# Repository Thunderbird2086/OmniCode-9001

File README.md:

# OmniCode:9001
A modular keyboard made up of three detachable untis.

*POGO pins are rendered with 5 pins only*

## Overview
OmniCode:9001 is the modular keyboards born in Hong Kong, engineered for control beyond limits. This highly customizable, open-source keyboard is designed for ergonomic comfort, maximum flexibility, and creative power. With magnetic connectors, hot-swappable blocks like GlyphMatrix, PhaseShift, and DeltaForm, OmniCode:9001 adapts to every workflow.  It is built with the RP2040 microcontroller for next-generation performance.  Ideal for makers and keyboard enthusiasts who demand the best.

## Sub Modules
- **Alpha Block:** GlyphMatrix taps into the visual power of language—glyphs as symbols, matrix as command stream. It’s the scriptwriter for your digital world.

- **Nav Block:** PhaseShift suggests rapid movement, shifting through modes or layers like teleportation. It’s your tactical array for traversing digital dimensions.

- **Num Block:** DeltaForm Already perfect. This name suggests modular transformation. Zoom, macros, data entry and it's all reborn in a shapeshifting format.

## Builds
* [BOM](bom/)
* [Build guides](doc/build.md)
* [Cases](cases/)

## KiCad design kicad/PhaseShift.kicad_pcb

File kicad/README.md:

# OmniCode:9001 PCB Designs

This directory contains all KiCad PCB design files for the OmniCode:9001 keyboard modules.

## Modules

### GlyphMatrix (Alpha Block)
The main typing module with a full ANSI layout.

**Features:**
- RP2040 microcontroller
- USB Type-C connector
- Hot-swappable MX switch sockets
- RGB LED support
- POGO pin connections for modular attachment

### PhaseShift (Nav Block)
Navigation and macro control module.

**Features:**
- Hot-swappable MX switch sockets
- RGB LED support
- POGO pin connections for modular attachment

### DeltaForm (Num Block)
Numeric keypad and additional macro keys.

**Features:**
- Hot-swappable MX switch sockets
- RGB LED support
- POGO pin connections for modular attachment

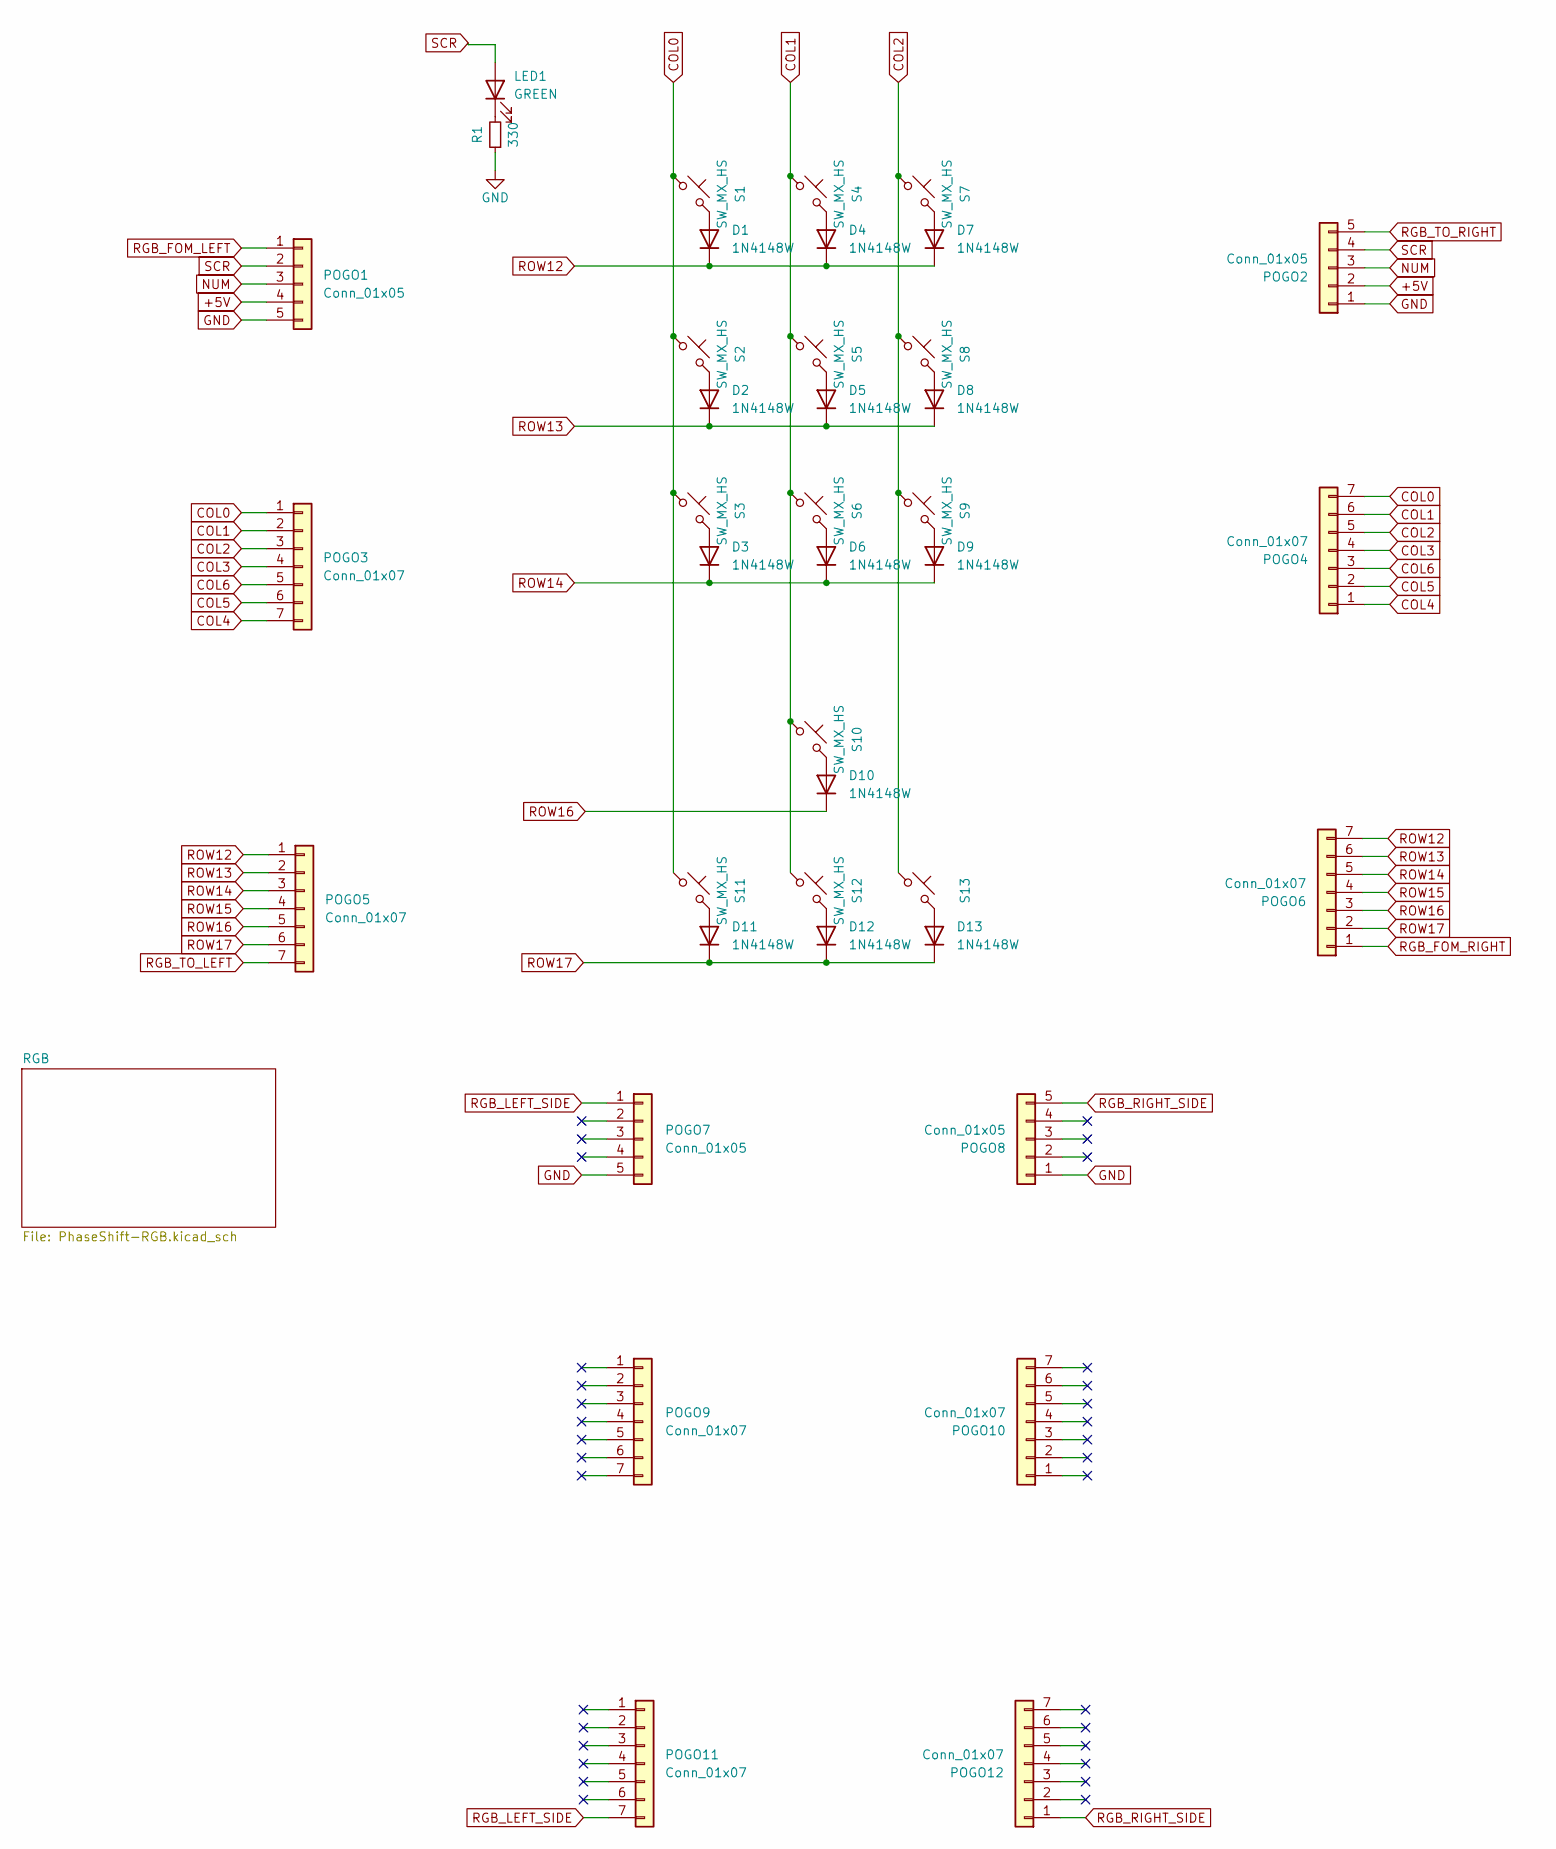
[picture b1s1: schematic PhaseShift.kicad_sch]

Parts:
D1, D2, D3, D4, D5, D6, D7, D8, D9, D10, D11, D12, D13: 1N4148W; D3_SMD; LCSC C7420318
LED1: GREEN; LED_0603_1608Metric_Pad1.05x0.95mm_HandSolder; LCSC C84264
POGO1, POGO2: Conn_01x05; Pogopin_1x05_P2.54mm_Curved
POGO3, POGO4, POGO5, POGO6: Conn_01x07; Pogopin_1x07_P2.54mm_Curved
POGO7, POGO8: Conn_01x05; Pogopin_1x05_P2.54mm
POGO9, POGO10, POGO11, POGO12: Conn_01x07; Pogopin_1x07_P2.54mm
R1: 330; R_0603_1608Metric; LCSC C23138
S1, S2, S3, S4, S5, S6, S7, S8, S9, S10, S11, S12: SW_MX_HS; SW_MX_HS_1u; LCSC C9900021274
S13: SW_MX_HS_1u; LCSC C9900021274

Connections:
+5V: POGO1.4, POGO2.2; also elsewhere on the board
COL0: POGO3.1, POGO4.7, S1.2, S2.2, S3.2, S11.2
COL1: POGO3.2, POGO4.6, S4.2, S5.2, S6.2, S10.2, S12.2
COL2: POGO3.3, POGO4.5, S7.2, S8.2, S9.2, S13.2
COL3: POGO3.4, POGO4.4
COL4: POGO3.7, POGO4.1
COL5: POGO3.6, POGO4.2
COL6: POGO3.5, POGO4.3
GND: POGO1.5, POGO2.1, POGO7.5, POGO8.1, R1.1; also elsewhere on the board
NUM: POGO1.3, POGO2.3
unnamed: D1.2 (A), S1.1
unnamed: D2.2 (A), S2.1
unnamed: D3.2 (A), S3.1
unnamed: D4.2 (A), S4.1
unnamed: D5.2 (A), S5.1
unnamed: D6.2 (A), S6.1
unnamed: D7.2 (A), S7.1
unnamed: D8.2 (A), S8.1
unnamed: D9.2 (A), S9.1
unnamed: D10.2 (A), S10.1
unnamed: D11.2 (A), S11.1
unnamed: D12.2 (A), S12.1
unnamed: D13.2 (A), S13.1
unnamed: LED1.1 (K), R1.2
RGB_FOM_LEFT: POGO1.1; also elsewhere on the board
RGB_FOM_RIGHT: POGO6.1; also elsewhere on the board
RGB_LEFT_SIDE: POGO7.1, POGO11.7
RGB_RIGHT_SIDE: POGO8.5, POGO12.1
RGB_TO_LEFT: POGO5.7; also elsewhere on the board
RGB_TO_RIGHT: POGO2.5; also elsewhere on the board
ROW12: D1.1 (K), D4.1 (K), D7.1 (K), POGO5.1, POGO6.7
ROW13: D2.1 (K), D5.1 (K), D8.1 (K), POGO5.2, POGO6.6
ROW14: D3.1 (K), D6.1 (K), D9.1 (K), POGO5.3, POGO6.5
ROW15: POGO5.4, POGO6.4
ROW16: D10.1 (K), POGO5.5, POGO6.3
ROW17: D11.1 (K), D12.1 (K), D13.1 (K), POGO5.6, POGO6.2
SCR: LED1.2 (A), POGO1.2, POGO2.4

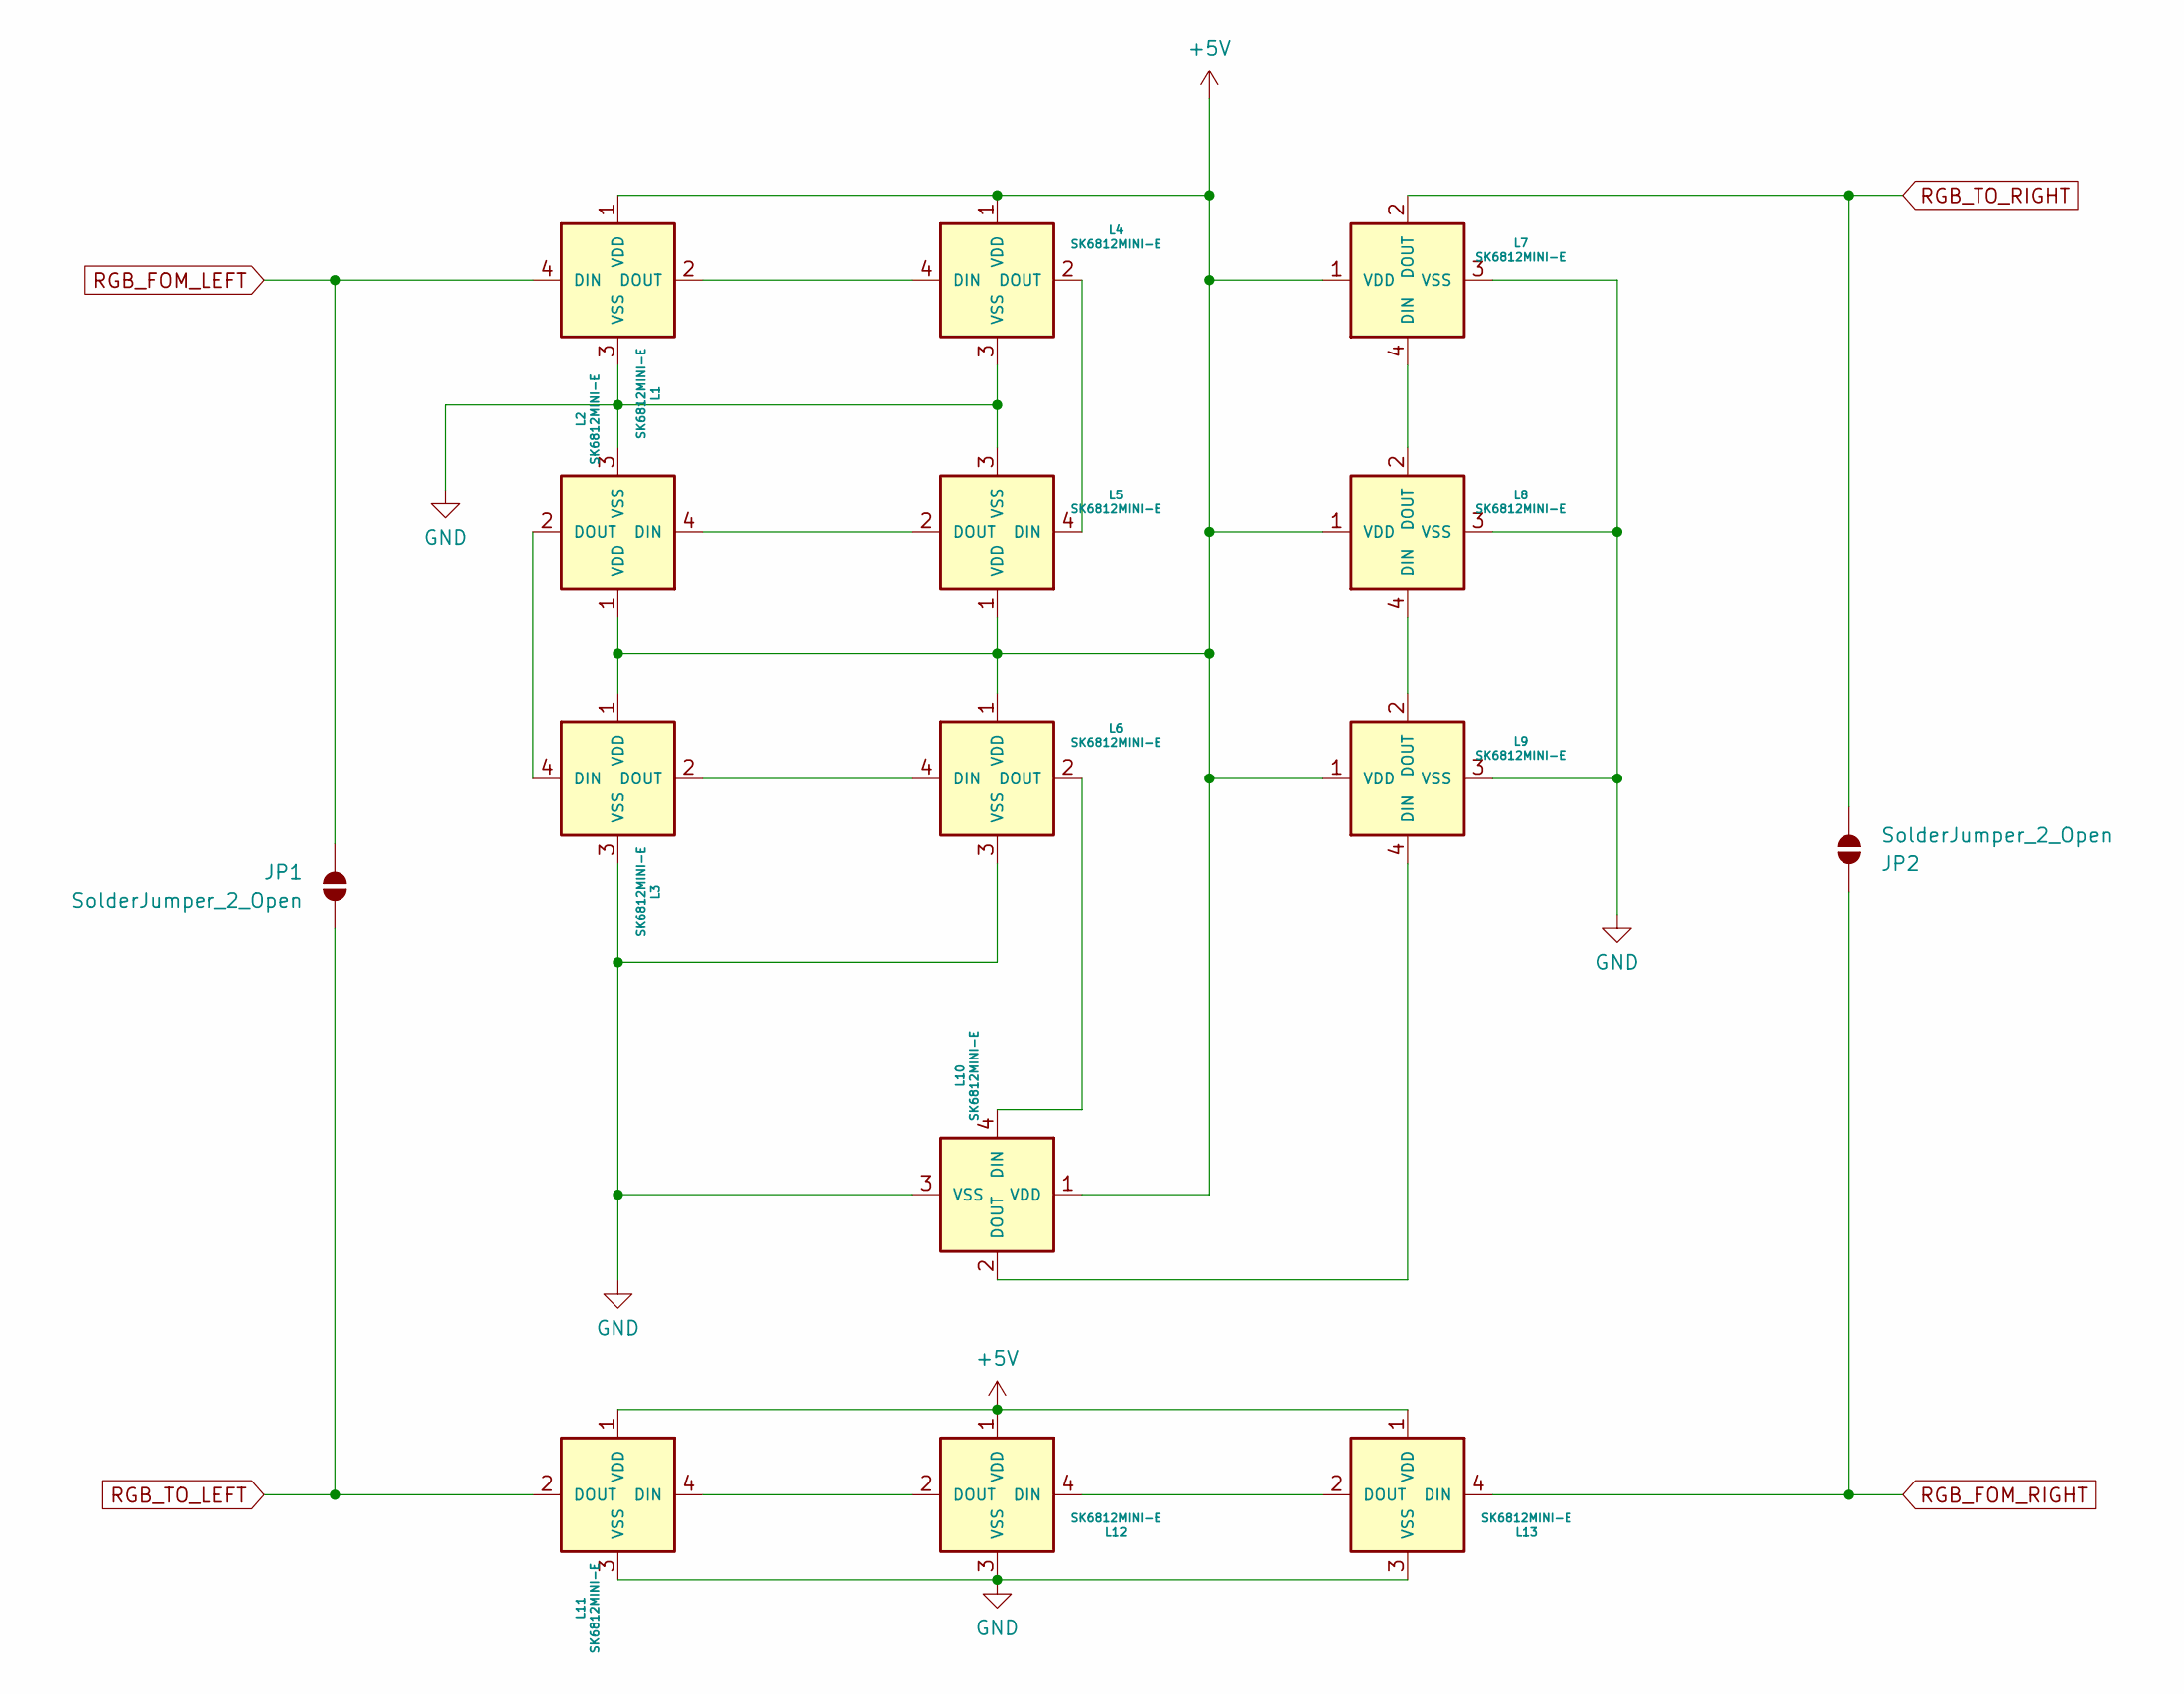
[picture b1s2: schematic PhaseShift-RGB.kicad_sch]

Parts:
JP1, JP2: SolderJumper_2_Open; SolderJumper-2_P1.3mm_Open_TrianglePad1.0x1.5mm
L1, L2, L3, L4, L5, L6, L7, L8, L9, L10, L11, L12, L13: SK6812MINI-E; LED_SK6812MINI-E; LCSC C7420318

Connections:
+5V: L1.1 (VDD), L2.1 (VDD), L3.1 (VDD), L4.1 (VDD), L5.1 (VDD), L6.1 (VDD), L7.1 (VDD), L8.1 (VDD), L9.1 (VDD), L10.1 (VDD), L11.1 (VDD), L12.1 (VDD), L13.1 (VDD); also elsewhere on the board
GND: L1.3 (VSS), L2.3 (VSS), L3.3 (VSS), L4.3 (VSS), L5.3 (VSS), L6.3 (VSS), L7.3 (VSS), L8.3 (VSS), L9.3 (VSS), L10.3 (VSS), L11.3 (VSS), L12.3 (VSS), L13.3 (VSS); also elsewhere on the board
unnamed: L1.2 (DOUT), L4.4 (DIN)
unnamed: L2.4 (DIN), L5.2 (DOUT)
unnamed: L2.2 (DOUT), L3.4 (DIN)
unnamed: L3.2 (DOUT), L6.4 (DIN)
unnamed: L4.2 (DOUT), L5.4 (DIN)
unnamed: L7.4 (DIN), L8.2 (DOUT)
unnamed: L8.4 (DIN), L9.2 (DOUT)
unnamed: L6.2 (DOUT), L10.4 (DIN)
unnamed: L9.4 (DIN), L10.2 (DOUT)
unnamed: L11.4 (DIN), L12.2 (DOUT)
unnamed: L12.4 (DIN), L13.2 (DOUT)
RGB_FOM_LEFT: JP1.2 (B), L1.4 (DIN); also elsewhere on the board
RGB_FOM_RIGHT: JP2.2 (B), L13.4 (DIN); also elsewhere on the board
RGB_TO_LEFT: JP1.1 (A), L11.2 (DOUT); also elsewhere on the board
RGB_TO_RIGHT: JP2.1 (A), L7.2 (DOUT); also elsewhere on the board

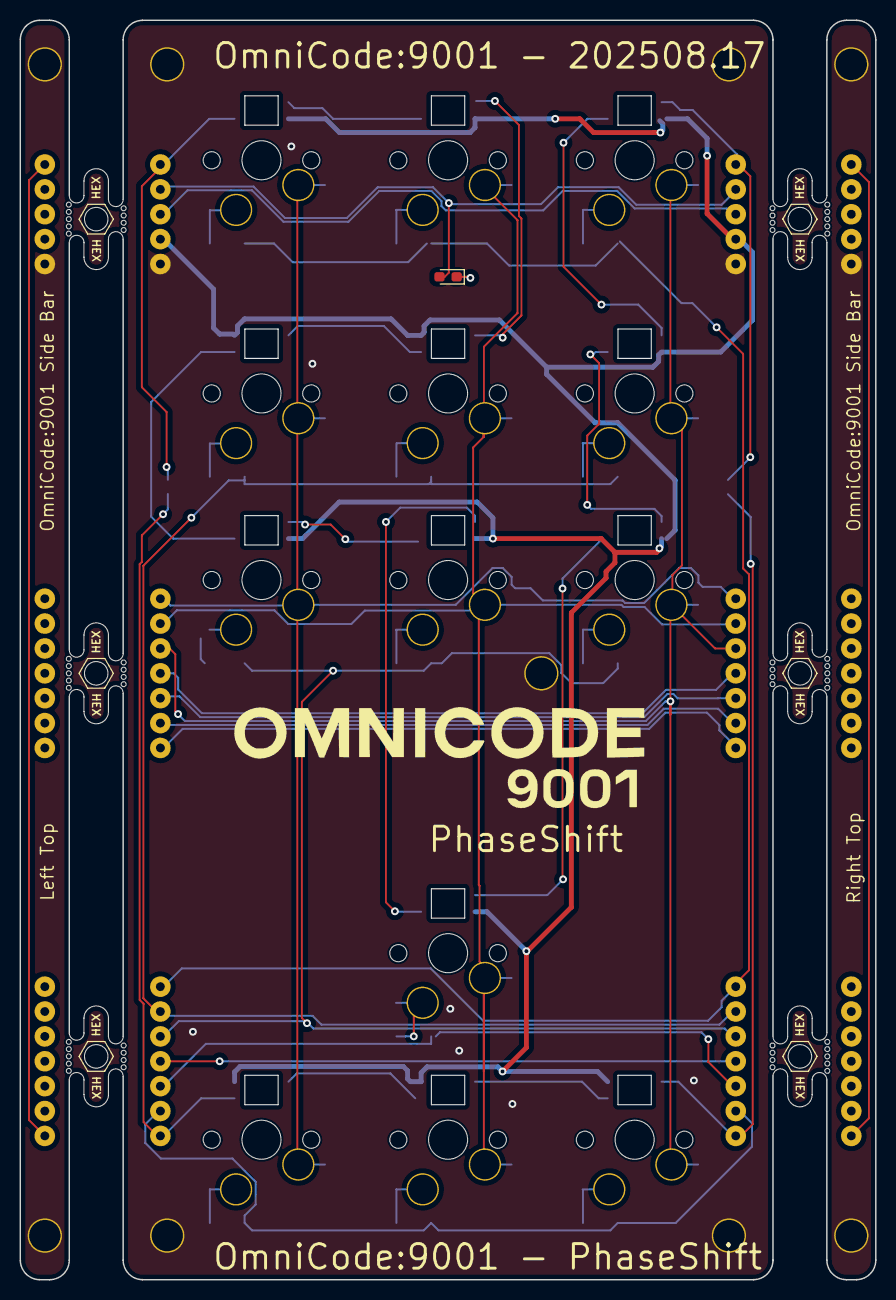
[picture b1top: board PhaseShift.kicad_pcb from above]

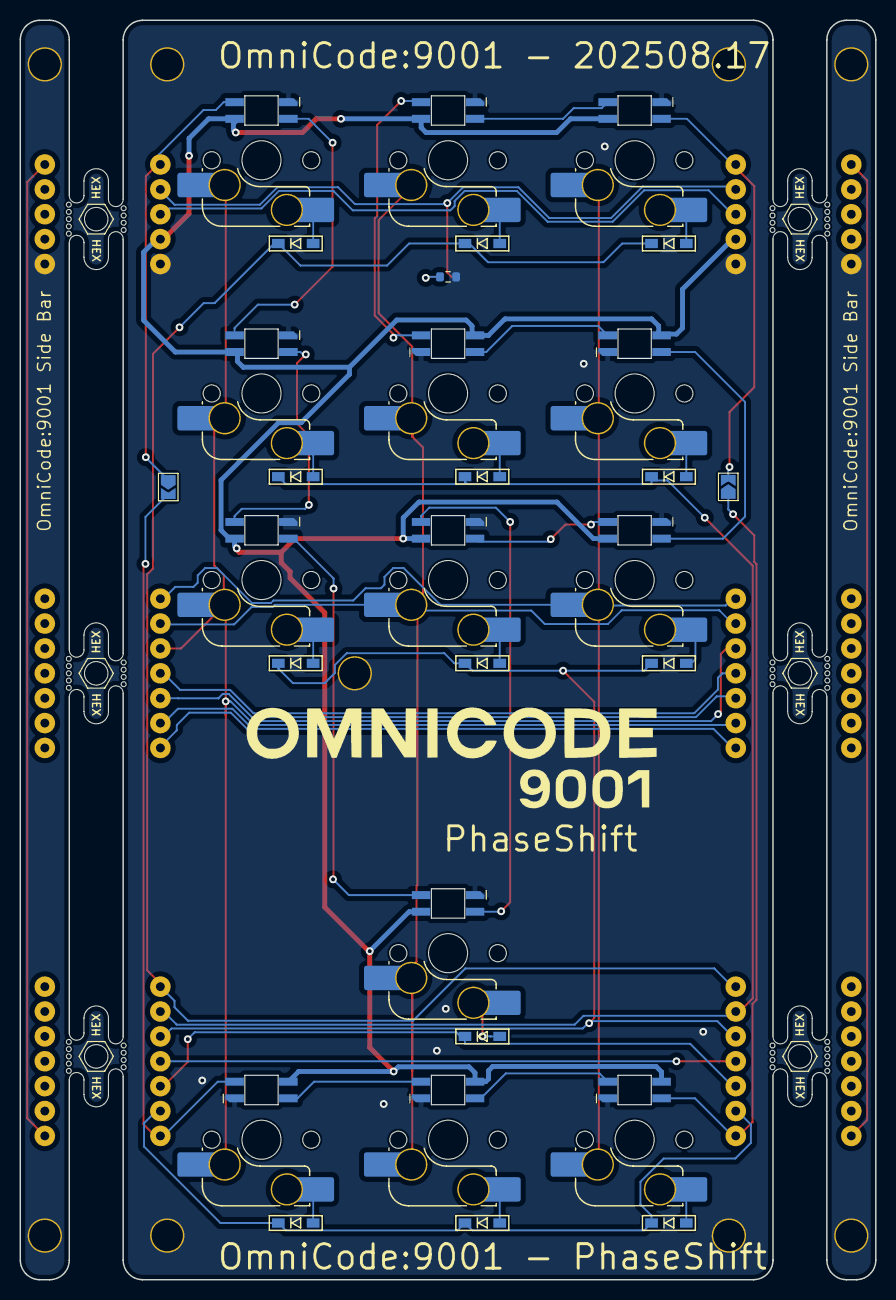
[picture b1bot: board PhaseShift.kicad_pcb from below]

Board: 2 copper layers, 87.4 x 128.6 mm, 70 parts (48 on the bottom side), 48 nets.

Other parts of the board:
H1, H2, H3, H4, H5, H6, H7, H8, H9: MountingHole_3.2mm_Pad
X1, X2, X3, X4, X5, X6: 5.5mm; mousebites_5p5mm_easysnap

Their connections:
GND: H1.1, H2.1, H3.1, H4.1, H5.1, H6.1, H7.1, H8.1, H9.1; also elsewhere on the board

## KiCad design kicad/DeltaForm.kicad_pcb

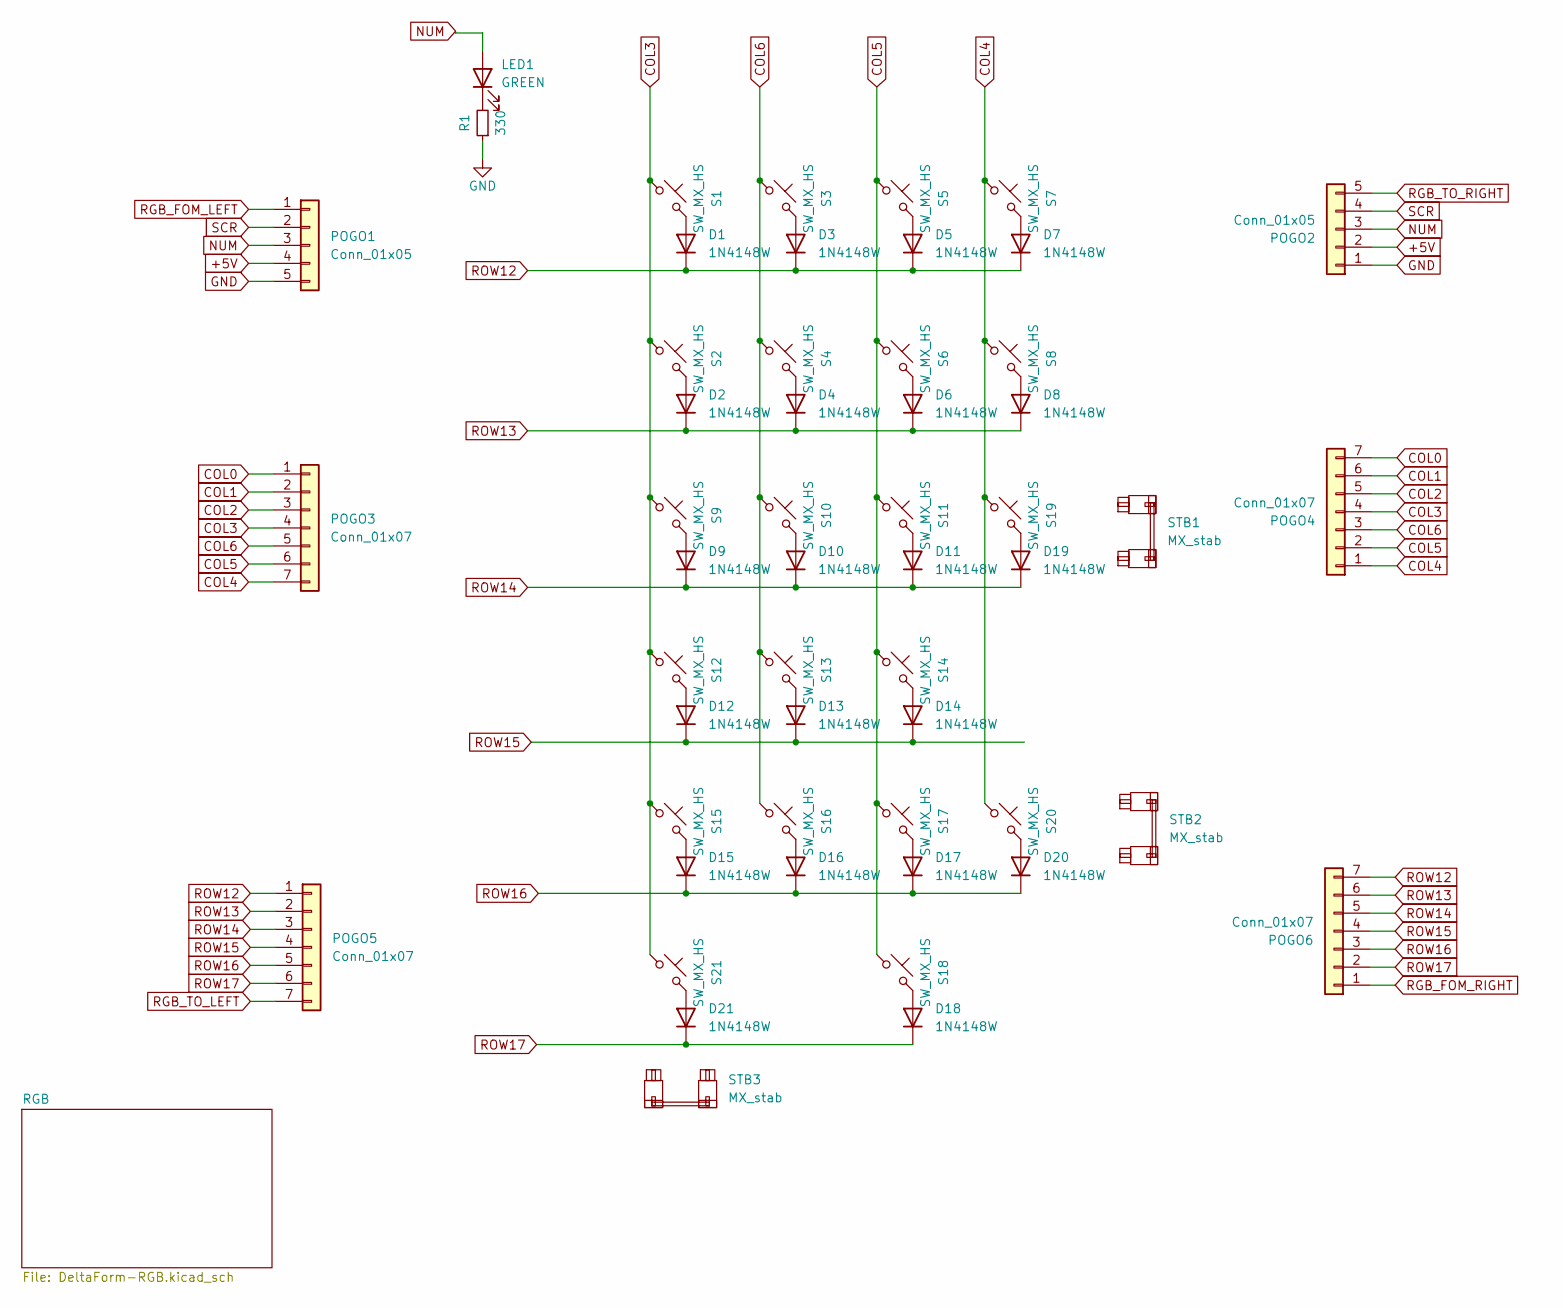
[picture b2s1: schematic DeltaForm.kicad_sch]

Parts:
D1, D2, D3, D4, D5, D6, D7, D8, D9, D10, D11, D12, D13, D14, D15, D16, D17, D18, D19, D20, D21: 1N4148W; D3_SMD; LCSC C7420318
LED1: GREEN; LED_0603_1608Metric_Pad1.05x0.95mm_HandSolder; LCSC C84264
POGO1, POGO2: Conn_01x05; Pogopin_1x05_P2.54mm_Curved
POGO3, POGO4, POGO5, POGO6: Conn_01x07; Pogopin_1x07_P2.54mm_Curved
R1: 330; R_0603_1608Metric; LCSC C23138
S1, S2, S3, S4, S5, S6, S7, S8, S9, S10, S11, S12, S13, S14, S15, S16, S17, S18, S19, S20: SW_MX_HS; SW_MX_HS_1u; LCSC C9900021274
S21: SW_MX_HS; SW_MX_HS_2u; LCSC C9900021274
STB1, STB2, STB3: MX_stab; Stabilizer_Cherry_MX_2.00u

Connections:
+5V: POGO1.4, POGO2.2; also elsewhere on the board
COL0: POGO3.1, POGO4.7
COL1: POGO3.2, POGO4.6
COL2: POGO3.3, POGO4.5
COL3: POGO3.4, POGO4.4, S1.2, S2.2, S9.2, S12.2, S15.2, S21.2
COL4: POGO3.7, POGO4.1, S7.2, S8.2, S19.2, S20.2
COL5: POGO3.6, POGO4.2, S5.2, S6.2, S11.2, S14.2, S17.2, S18.2
COL6: POGO3.5, POGO4.3, S3.2, S4.2, S10.2, S13.2, S16.2
GND: POGO1.5, POGO2.1, R1.1; also elsewhere on the board
NUM: LED1.2 (A), POGO1.3, POGO2.3
unnamed: D1.2 (A), S1.1
unnamed: D2.2 (A), S2.1
unnamed: D3.2 (A), S3.1
unnamed: D4.2 (A), S4.1
unnamed: D5.2 (A), S5.1
unnamed: D6.2 (A), S6.1
unnamed: D7.2 (A), S7.1
unnamed: D8.2 (A), S8.1
unnamed: D9.2 (A), S9.1
unnamed: D10.2 (A), S10.1
unnamed: D11.2 (A), S11.1
unnamed: D12.2 (A), S12.1
unnamed: D13.2 (A), S13.1
unnamed: D14.2 (A), S14.1
unnamed: D15.2 (A), S15.1
unnamed: D16.2 (A), S16.1
unnamed: D17.2 (A), S17.1
unnamed: D18.2 (A), S18.1
unnamed: D19.2 (A), S19.1
unnamed: D20.2 (A), S20.1
unnamed: D21.2 (A), S21.1
unnamed: LED1.1 (K), R1.2
RGB_FOM_LEFT: POGO1.1; also elsewhere on the board
RGB_FOM_RIGHT: POGO6.1; also elsewhere on the board
RGB_TO_LEFT: POGO5.7; also elsewhere on the board
RGB_TO_RIGHT: POGO2.5; also elsewhere on the board
ROW12: D1.1 (K), D3.1 (K), D5.1 (K), D7.1 (K), POGO5.1, POGO6.7
ROW13: D2.1 (K), D4.1 (K), D6.1 (K), D8.1 (K), POGO5.2, POGO6.6
ROW14: D9.1 (K), D10.1 (K), D11.1 (K), D19.1 (K), POGO5.3, POGO6.5
ROW15: D12.1 (K), D13.1 (K), D14.1 (K), POGO5.4, POGO6.4
ROW16: D15.1 (K), D16.1 (K), D17.1 (K), D20.1 (K), POGO5.5, POGO6.3
ROW17: D18.1 (K), D21.1 (K), POGO5.6, POGO6.2
SCR: POGO1.2, POGO2.4

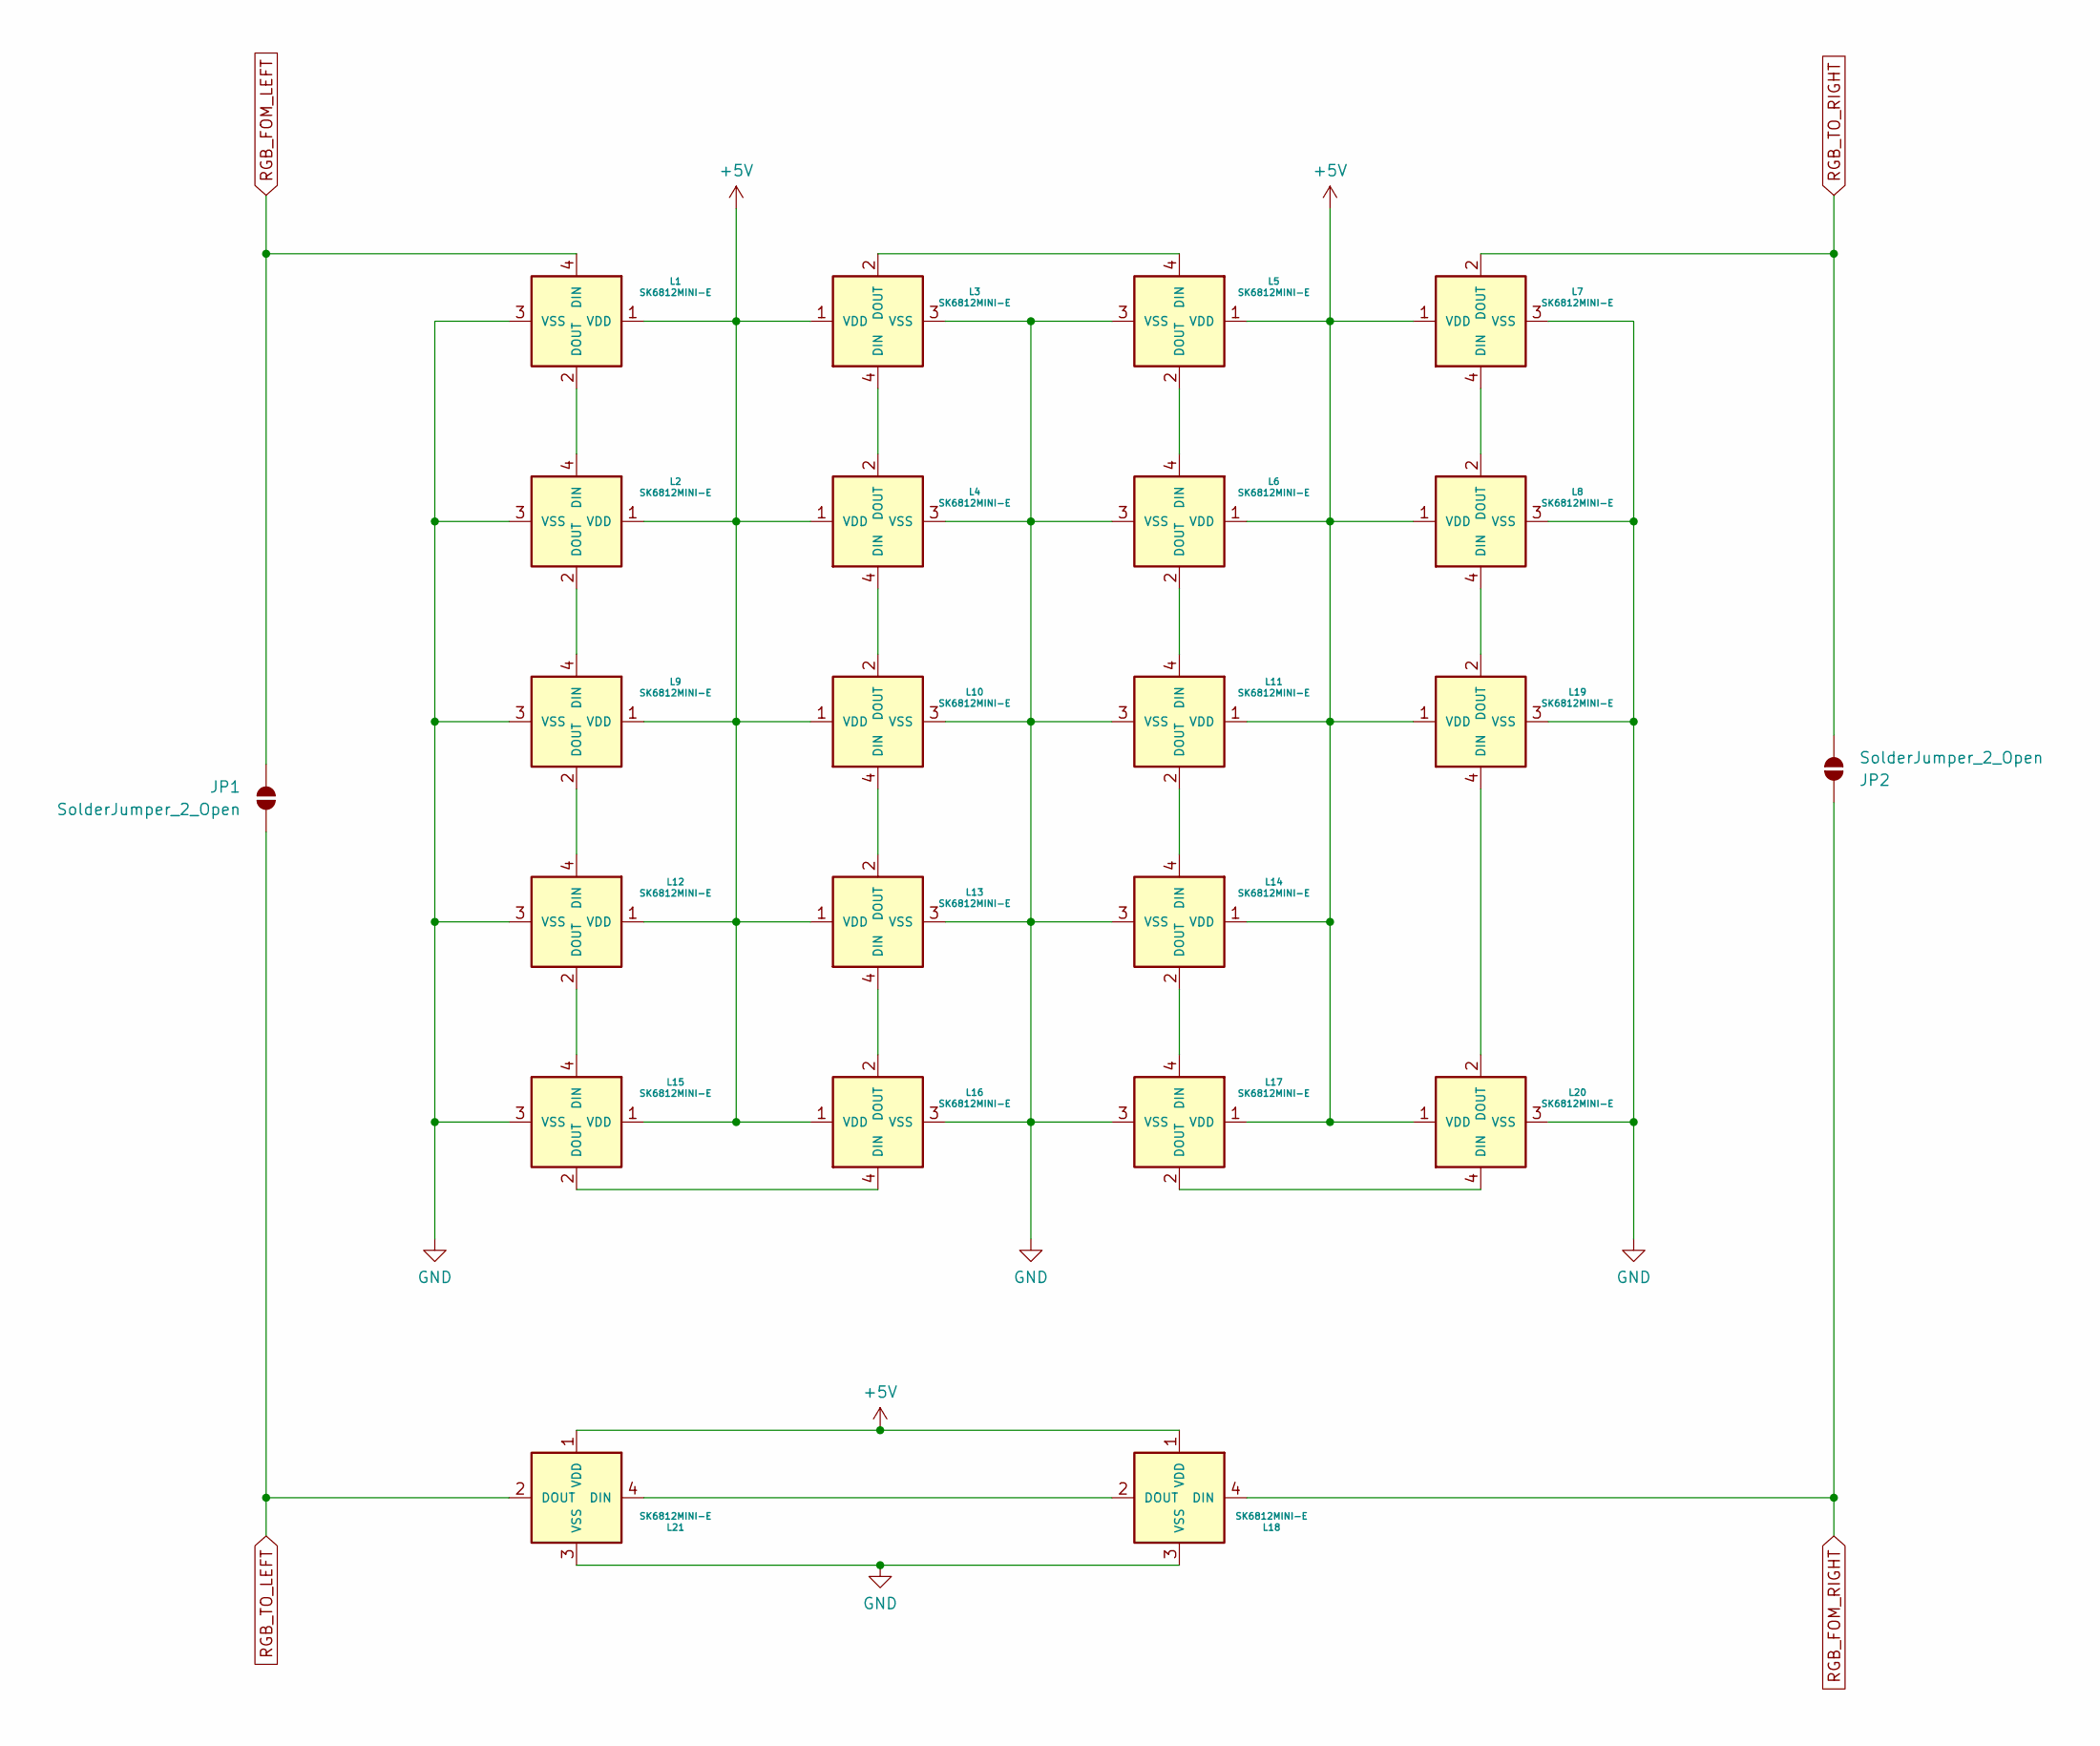
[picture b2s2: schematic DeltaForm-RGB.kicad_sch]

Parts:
JP1, JP2: SolderJumper_2_Open; SolderJumper-2_P1.3mm_Open_TrianglePad1.0x1.5mm
L1, L2, L3, L4, L5, L6, L7, L8, L9, L10, L11, L12, L13, L14, L15, L16, L17, L18, L19, L20, L21: SK6812MINI-E; LED_SK6812MINI-E; LCSC C7420318

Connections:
+5V: L1.1 (VDD), L2.1 (VDD), L3.1 (VDD), L4.1 (VDD), L5.1 (VDD), L6.1 (VDD), L7.1 (VDD), L8.1 (VDD), L9.1 (VDD), L10.1 (VDD), L11.1 (VDD), L12.1 (VDD), L13.1 (VDD), L14.1 (VDD), L15.1 (VDD), L16.1 (VDD), L17.1 (VDD), L18.1 (VDD), L19.1 (VDD), L20.1 (VDD), L21.1 (VDD); also elsewhere on the board
GND: L1.3 (VSS), L2.3 (VSS), L3.3 (VSS), L4.3 (VSS), L5.3 (VSS), L6.3 (VSS), L7.3 (VSS), L8.3 (VSS), L9.3 (VSS), L10.3 (VSS), L11.3 (VSS), L12.3 (VSS), L13.3 (VSS), L14.3 (VSS), L15.3 (VSS), L16.3 (VSS), L17.3 (VSS), L18.3 (VSS), L19.3 (VSS), L20.3 (VSS), L21.3 (VSS); also elsewhere on the board
unnamed: L1.2 (DOUT), L2.4 (DIN)
unnamed: L2.2 (DOUT), L9.4 (DIN)
unnamed: L3.4 (DIN), L4.2 (DOUT)
unnamed: L3.2 (DOUT), L5.4 (DIN)
unnamed: L5.2 (DOUT), L6.4 (DIN)
unnamed: L7.4 (DIN), L8.2 (DOUT)
unnamed: L10.4 (DIN), L13.2 (DOUT)
unnamed: L4.4 (DIN), L10.2 (DOUT)
unnamed: L6.2 (DOUT), L11.4 (DIN)
unnamed: L11.2 (DOUT), L14.4 (DIN)
unnamed: L9.2 (DOUT), L12.4 (DIN)
unnamed: L12.2 (DOUT), L15.4 (DIN)
unnamed: L13.4 (DIN), L16.2 (DOUT)
unnamed: L14.2 (DOUT), L17.4 (DIN)
unnamed: L15.2 (DOUT), L16.4 (DIN)
unnamed: L17.2 (DOUT), L20.4 (DIN)
unnamed: L18.2 (DOUT), L21.4 (DIN)
unnamed: L19.4 (DIN), L20.2 (DOUT)
unnamed: L8.4 (DIN), L19.2 (DOUT)
RGB_FOM_LEFT: JP1.2 (B), L1.4 (DIN); also elsewhere on the board
RGB_FOM_RIGHT: JP2.2 (B), L18.4 (DIN); also elsewhere on the board
RGB_TO_LEFT: JP1.1 (A), L21.2 (DOUT); also elsewhere on the board
RGB_TO_RIGHT: JP2.1 (A), L7.2 (DOUT); also elsewhere on the board

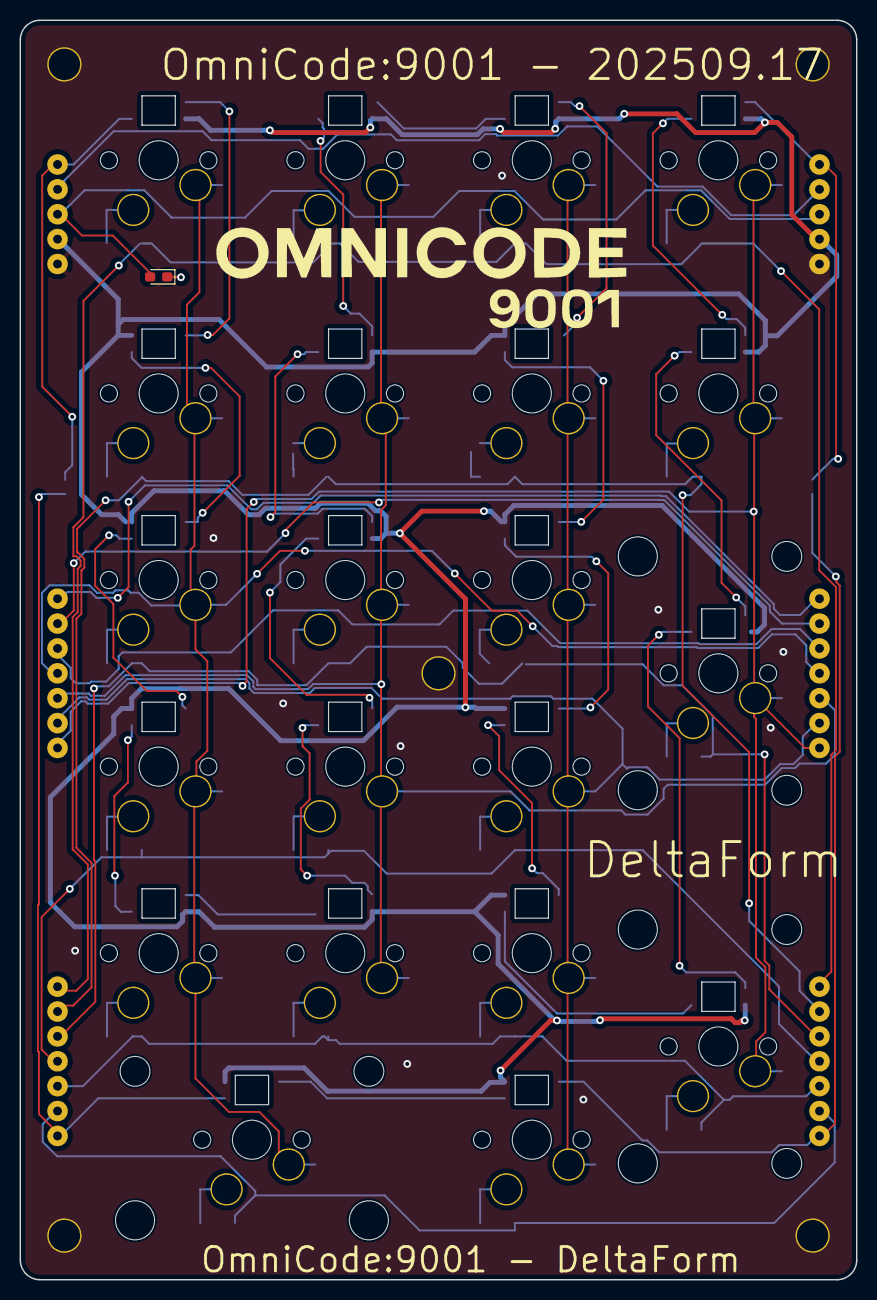
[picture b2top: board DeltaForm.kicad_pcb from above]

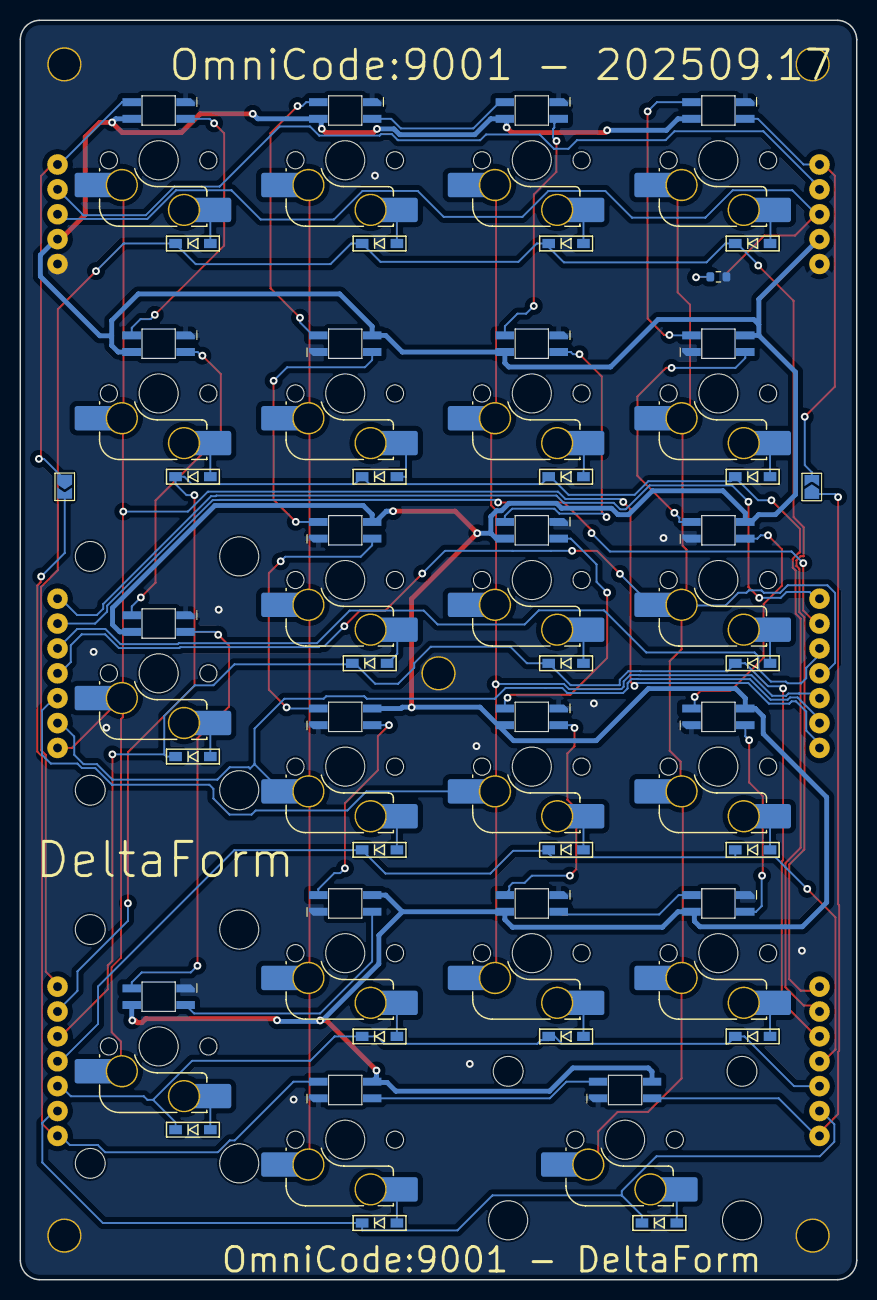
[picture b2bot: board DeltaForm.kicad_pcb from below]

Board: 2 copper layers, 85.4 x 128.6 mm, 81 parts (72 on the bottom side), 62 nets.

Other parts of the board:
H1, H2, H3, H4, H5: MountingHole_3.2mm_Pad

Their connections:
GND: H1.1, H2.1, H3.1, H4.1, H5.1; also elsewhere on the board
